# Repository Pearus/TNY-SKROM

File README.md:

# TNY-SKROM

This is a custom SKROM board for the TinyTendo handheld console by <a href="https://github.com/Redherring32">Redherring32</a>. This board replicates <a href="https://www.nesdev.org/wiki/MMC1">standard SKROM NES boards</a>. SKROM uses CHR ROM and PRG RAM, and can have a backup battery if the game saves data on the PRG RAM. You can also make SLROM games with this board and remove the PRG RAM.

To use this board, you must remove an MMC1 mapper from an original NES board, clip the leads flush to the package, sand it, and mount it where U1 is indicated. Since these boards use the 39SF040 for both PRG and CHR ROM, you should use FamiROM or some other utility to duplicate the ROM files to completely fill up the entire space on the Flash chip if necessary.

# TNY-SKROM Board Characteristics

- Thickness: 1.6 mm
- Surface Finish: ENIG
- Chamfered edges (45°)
- Compatible NES board types: SAROM, SBROM, SCROM, SEROM, SFROM, SHROM, SIROM, SJROM, **SKROM**, SLROM
- Compatible NES board types with CHR RAM flex: SGROM, SMROM, SNROM, SUROM

# How to Use This Board

*Note: Do not solder U2 and U3 to the board before programming them.*

SAROM and SKROM games require every component on the board. **DO NOT** solder bridge the pads labelled "NO BATT."

SJROM games are the same as SAROM/SKROM, but without the battery, R1, D1, and D2. You must also bridge the two pads labelled "NO BATT" with solder.

SAROM, SBROM, SCROM, SEROM, SFROM, SHROM, and SLROM games are the same as SJROM, but without U4, R2, R4, C5, and C6. You don't need to bridge the "NO BATT" pads.

SGROM, SMROM, SNROM, and SUROM games require the included flex to fit an SRAM chip in place of the CHR ROM.

The solder jumpers must be bridged according to the NES board type you are trying to replicate.

| Jumper  | SA/SB/SC/SF/SI/SJ/SK/SL | SE/SH  | SG/SM/SU  | SN |
|:-------------------------------------:|:-------------------------------------:|:-------------------------------------:|:-------------------------------------:|:-------------------------------------:|
| CHR ROM  |  |   | Unbridged  | Unbridged  |
| CHR ROM/RAM  |  |   |   |   |
| SNROM  |  |   |   |   |
| SEROM/SHROM  |  |   |   |   |

## Flashing the Game

Prepare the ROM using FamiROM or other similar program, ensuring the entire 4Mbit space is filled for both the PRG and CHR components. You then need to program the 39SF040s before soldering them to the board. I use a <a href="https://www.embeddedcomputers.net/products/FlashcatUSB_XPORT/">FlashCat</a> with a <a href="https://www.embeddedcomputers.net/products/ParallelAdapters/">TSOP-32 adapter (Type B)</a> to achieve this.

# Bill of Materials

Capacitors should be at least 16V rated. Resistor wattage is negligible.

| Reference Designator  | Part Number/Value | Footprint  |
| ------------- | ------------- | ------------- |
| B1  | CR2016 | CR2016  |
| C1  | 22 uF | 1206  |
| C2-C5  | 0.1 uF | 0603  |
| D1, D2  | <a href="https://www.mouser.com/ProductDetail/Vishay-Semiconductors/BAT54W-HG3-18?qs=BJlw7L4Cy79w8lzctLBe5g%3D%3D">BAT54</a> | SMA (SOD-123) |
| R1  | 1 kΩ | 0603  |
| R2  | 27 kΩ | 0603  |
| R3  | 10 kΩ | 0603  |
| U1  | MMC1  | SHRINKDIP24  |
| U2  | <a href="https://www.mouser.com/ProductDetail/Microchip-Technology/SST39SF040-70-4C-WHE?qs=Oo69DRhzroe%2FJKrgAmUE5Q%3D%3D">39SF040</a>  | TSOP32 (14mm) |
| U3 (ROM)  | <a href="https://www.mouser.com/ProductDetail/Microchip-Technology/SST39SF040-70-4C-WHE?qs=Oo69DRhzroe%2FJKrgAmUE5Q%3D%3D">39SF040</a>  | TSOP32 (14mm) |
| U3 (RAM)  | <a href="https://www.mouser.com/ProductDetail/Alliance-Memory/AS6C6264-55STCN?qs=LD2UibpCYJonFY2RVods7g%3D%3D">AS6C6264</a> or <a href="https://www.mouser.com/ProductDetail/870-IS61C64AL-10TLI">IS61C64AL-10TLI</a>  | TSOP28 |
| U4  | <a href="https://www.mouser.com/ProductDetail/Alliance-Memory/AS6C6264-55SCN?qs=LD2UibpCYJq5mmbqgDVBYw%3D%3D">AS6C6264</a>              | SOP28  / SOIC28 |

# Revision History

## v1.0

- Initial version

## License
<br />This work is licensed under a <a rel="license" href="http://creativecommons.org/licenses/by-sa/4.0/">Creative Commons Attribution-ShareAlike 4.0 International License</a>. You are able to copy and redistribute the material in any medium or format, as well as remix, transform, or build upon the material for any purpose (even commercial) - but you **must** give appropriate credit, provide a link to the license, and indicate if any changes were made.

## Credits

*Redherring32* - Creating the TinyTendo project.

*BucketMouse* - Original MMC3 and NROM cartridge designs for TinyTendo which this is an extension of.

*NESDev* - Wiki was heavily referenced as part of writing the schematic and troubleshooting.

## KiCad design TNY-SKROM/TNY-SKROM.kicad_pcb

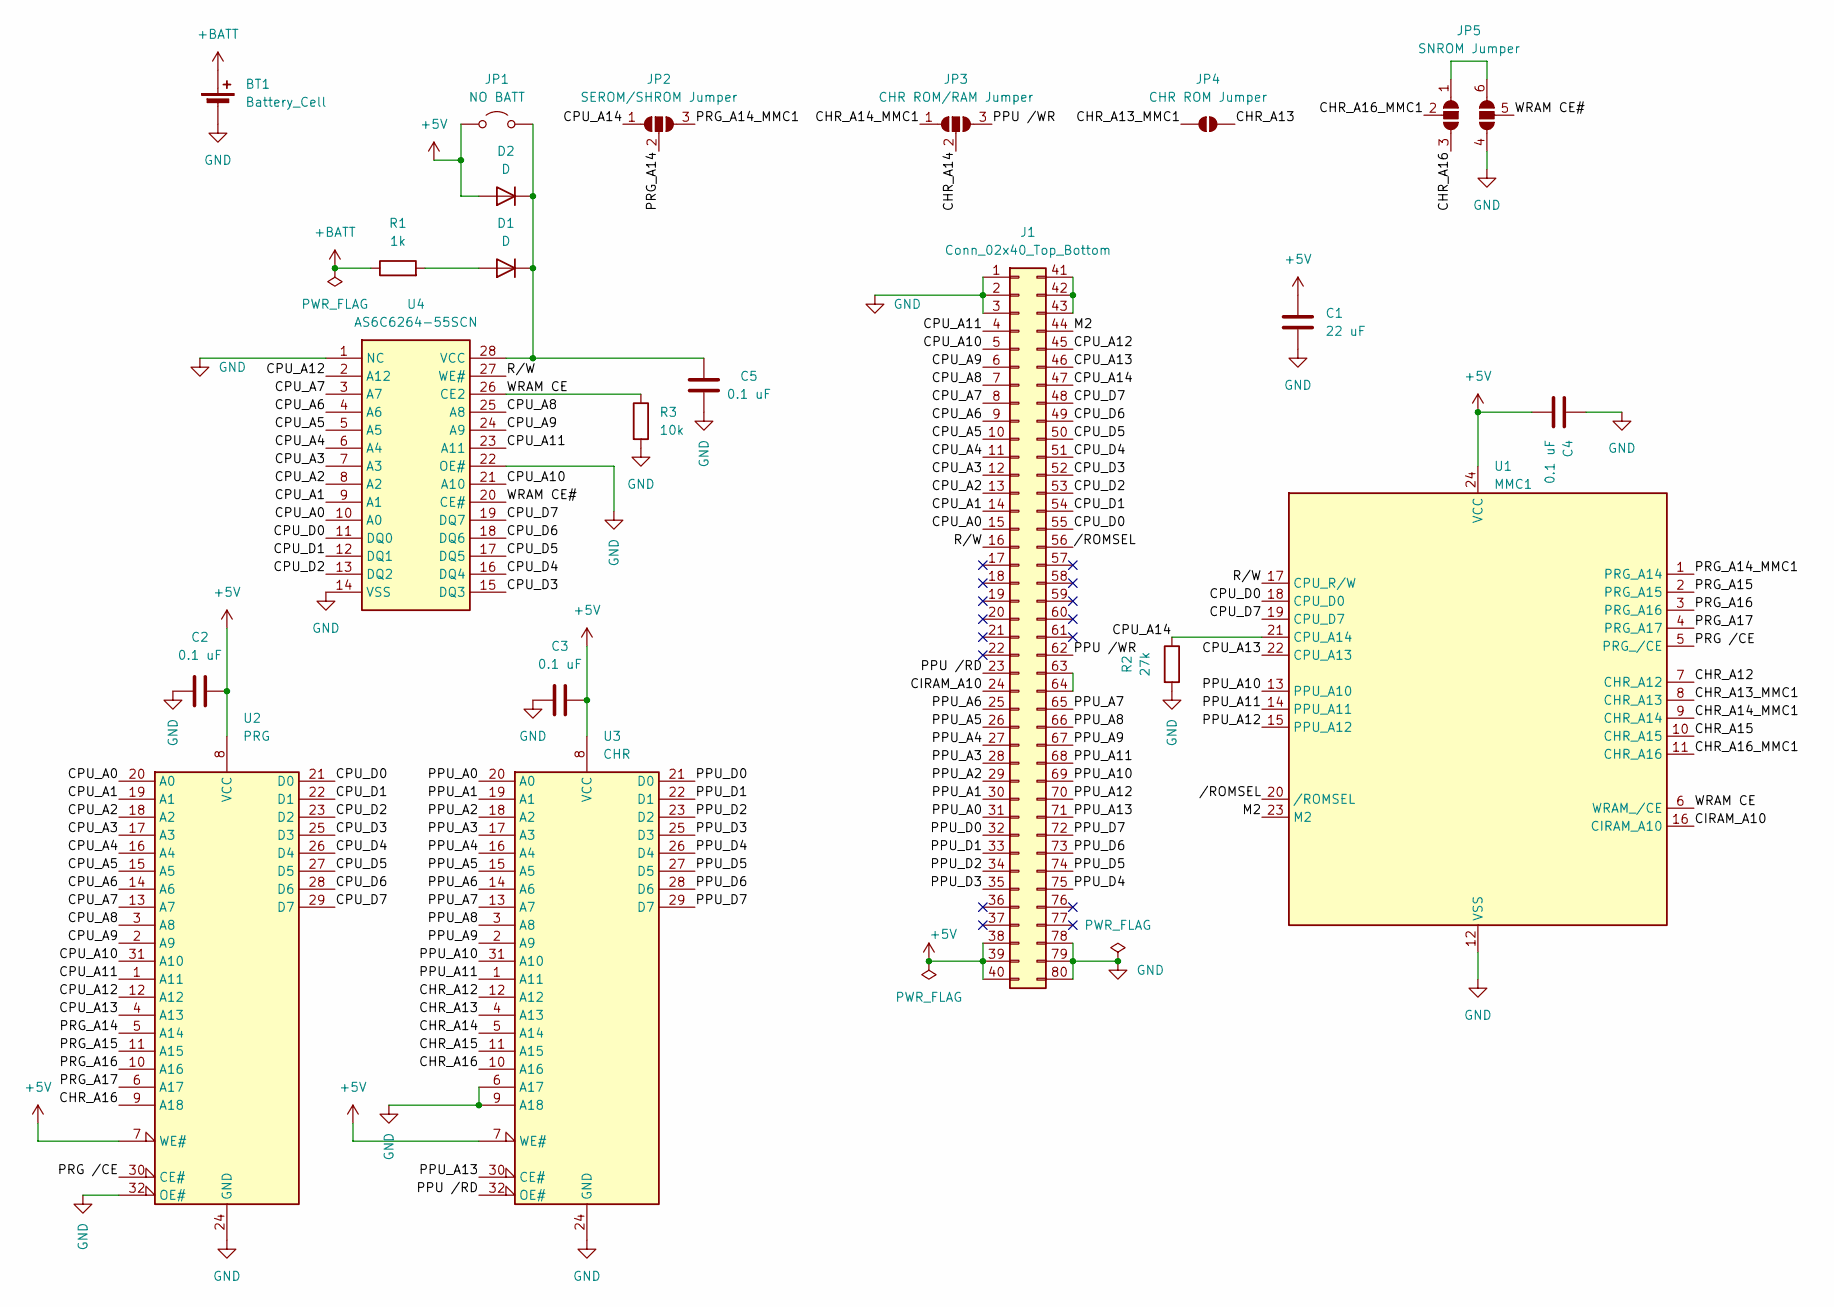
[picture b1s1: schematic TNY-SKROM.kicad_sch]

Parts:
BT1: Battery_Cell; Tabbed CR2016
C1: 22 uF; C_1206_3216Metric
C2, C3, C4, C5: 0.1 uF; C_0603_1608Metric
D1, D2: D; D_SOD-123
J1: Conn_02x40_Top_Bottom; TNY-SKROM Edge Connector
JP1: NO BATT; SolderJumper-2_P1.3mm_Open_Pad1.0x1.5mm
JP2: SEROM/SHROM Jumper; SEROM_SHROM Jumper
JP3: CHR ROM/RAM Jumper; CHR A14 Jumper
JP4: CHR ROM Jumper; CHR A13 Jumper
JP5: SNROM Jumper
R1: 1k; R_0603_1608Metric
R2: 27k; R_0603_1608Metric
R3: 10k; R_0603_1608Metric
U1: MMC1
U2: PRG; TSOP-32
U3: CHR; TSOP-32
U4: AS6C6264-55SCN; Manufacturer_Part_Number AS6C6264-55SCN; Mouser Part Number 913-AS6C6264-55SCN

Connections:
+5V: C1.1, C2.2, C3.1, C4.2, D2.2 (A), J1.38, J1.39, J1.40, JP1.1 (A), U1.24 (VCC), U2.7 (WE#), U2.8 (VCC), U3.7 (WE#), U3.8 (VCC)
+BATT: BT1.1 (+), R1.1
/CHR_A12: U1.7 (CHR_A12), U3.12 (A12)
/CHR_A13: JP4.2 (B), U3.4 (A13)
/CHR_A13_MMC1: JP4.1 (A), U1.8 (CHR_A13)
/CHR_A14: JP3.2 (C), U3.5 (A14)
/CHR_A14_MMC1: JP3.1 (A), U1.9 (CHR_A14)
/CHR_A15: U1.10 (CHR_A15), U3.11 (A15)
/CHR_A16: JP5.3 (B), U2.9 (A18), U3.10 (A16)
/CHR_A16_MMC1: JP5.2 (C), U1.11 (CHR_A16)
/CIRAM_A10: J1.24, U1.16 (CIRAM_A10)
/CPU_A0: J1.15, U2.20 (A0), U4.10 (A0)
/CPU_A1: J1.14, U2.19 (A1), U4.9 (A1)
/CPU_A2: J1.13, U2.18 (A2), U4.8 (A2)
/CPU_A3: J1.12, U2.17 (A3), U4.7 (A3)
/CPU_A4: J1.11, U2.16 (A4), U4.6 (A4)
/CPU_A5: J1.10, U2.15 (A5), U4.5 (A5)
/CPU_A6: J1.9, U2.14 (A6), U4.4 (A6)
/CPU_A7: J1.8, U2.13 (A7), U4.3 (A7)
/CPU_A8: J1.7, U2.3 (A8), U4.25 (A8)
/CPU_A9: J1.6, U2.2 (A9), U4.24 (A9)
/CPU_A10: J1.5, U2.31 (A10), U4.21 (A10)
/CPU_A11: J1.4, U2.1 (A11), U4.23 (A11)
/CPU_A12: J1.45, U2.12 (A12), U4.2 (A12)
/CPU_A13: J1.46, U1.22 (CPU_A13), U2.4 (A13)
/CPU_A14: J1.47, JP2.1 (A), R2.1, U1.21 (CPU_A14)
/CPU_D0: J1.55, U1.18 (CPU_D0), U2.21 (D0), U4.11 (DQ0)
/CPU_D1: J1.54, U2.22 (D1), U4.12 (DQ1)
/CPU_D2: J1.53, U2.23 (D2), U4.13 (DQ2)
/CPU_D3: J1.52, U2.25 (D3), U4.15 (DQ3)
/CPU_D4: J1.51, U2.26 (D4), U4.16 (DQ4)
/CPU_D5: J1.50, U2.27 (D5), U4.17 (DQ5)
/CPU_D6: J1.49, U2.28 (D6), U4.18 (DQ6)
/CPU_D7: J1.48, U1.19 (CPU_D7), U2.29 (D7), U4.19 (DQ7)
/M2: J1.44, U1.23 (M2)
/PPU /RD: J1.23, U3.32 (OE#)
/PPU /WR: J1.62, JP3.3 (B)
/PPU_A0: J1.31, U3.20 (A0)
/PPU_A1: J1.30, U3.19 (A1)
/PPU_A2: J1.29, U3.18 (A2)
/PPU_A3: J1.28, U3.17 (A3)
/PPU_A4: J1.27, U3.16 (A4)
/PPU_A5: J1.26, U3.15 (A5)
/PPU_A6: J1.25, U3.14 (A6)
/PPU_A7: J1.65, U3.13 (A7)
/PPU_A8: J1.66, U3.3 (A8)
/PPU_A9: J1.67, U3.2 (A9)
/PPU_A10: J1.69, U1.13 (PPU_A10), U3.31 (A10)
/PPU_A11: J1.68, U1.14 (PPU_A11), U3.1 (A11)
/PPU_A12: J1.70, U1.15 (PPU_A12)
/PPU_A13: J1.71, U3.30 (CE#)
/PPU_D0: J1.32, U3.21 (D0)
/PPU_D1: J1.33, U3.22 (D1)
/PPU_D2: J1.34, U3.23 (D2)
/PPU_D3: J1.35, U3.25 (D3)
/PPU_D4: J1.75, U3.26 (D4)
/PPU_D5: J1.74, U3.27 (D5)
/PPU_D6: J1.73, U3.28 (D6)
/PPU_D7: J1.72, U3.29 (D7)
/PRG /CE: U1.5 (PRG_/CE), U2.30 (CE#)
/PRG_A14: JP2.2 (C), U2.5 (A14)
/PRG_A14_MMC1: JP2.3 (B), U1.1 (PRG_A14)
/PRG_A15: U1.2 (PRG_A15), U2.11 (A15)
/PRG_A16: U1.3 (PRG_A16), U2.10 (A16)
/PRG_A17: U1.4 (PRG_A17), U2.6 (A17)
/R/W: J1.16, U1.17 (CPU_R/W), U4.27 (WE#)
/WRAM CE: R3.1, U1.6 (WRAM_/CE), U4.26 (CE2)
/WRAM CE#: JP5.5 (C), U4.20 (CE#)
//ROMSEL: J1.56, U1.20 (/ROMSEL)
GND: BT1.2 (-), C1.2, C2.1, C3.2, C4.1, C5.2, J1.1, J1.2, J1.3, J1.78, J1.79, J1.80, JP5.4 (A), R2.2, R3.2, U1.12 (VSS), U2.24 (GND), U2.32 (OE#), U3.6 (A17), U3.9 (A18), U3.24 (GND), U4.1 (NC), U4.14 (VSS), U4.22 (OE#)
unnamed: D1.2 (A), R1.2
unnamed: C5.1, D1.1 (K), D2.1 (K), JP1.2 (B), U4.28 (VCC)
unnamed: J1.41, J1.42, J1.43
unnamed: J1.63, J1.64
unnamed: JP5.1 (A), JP5.6 (B)

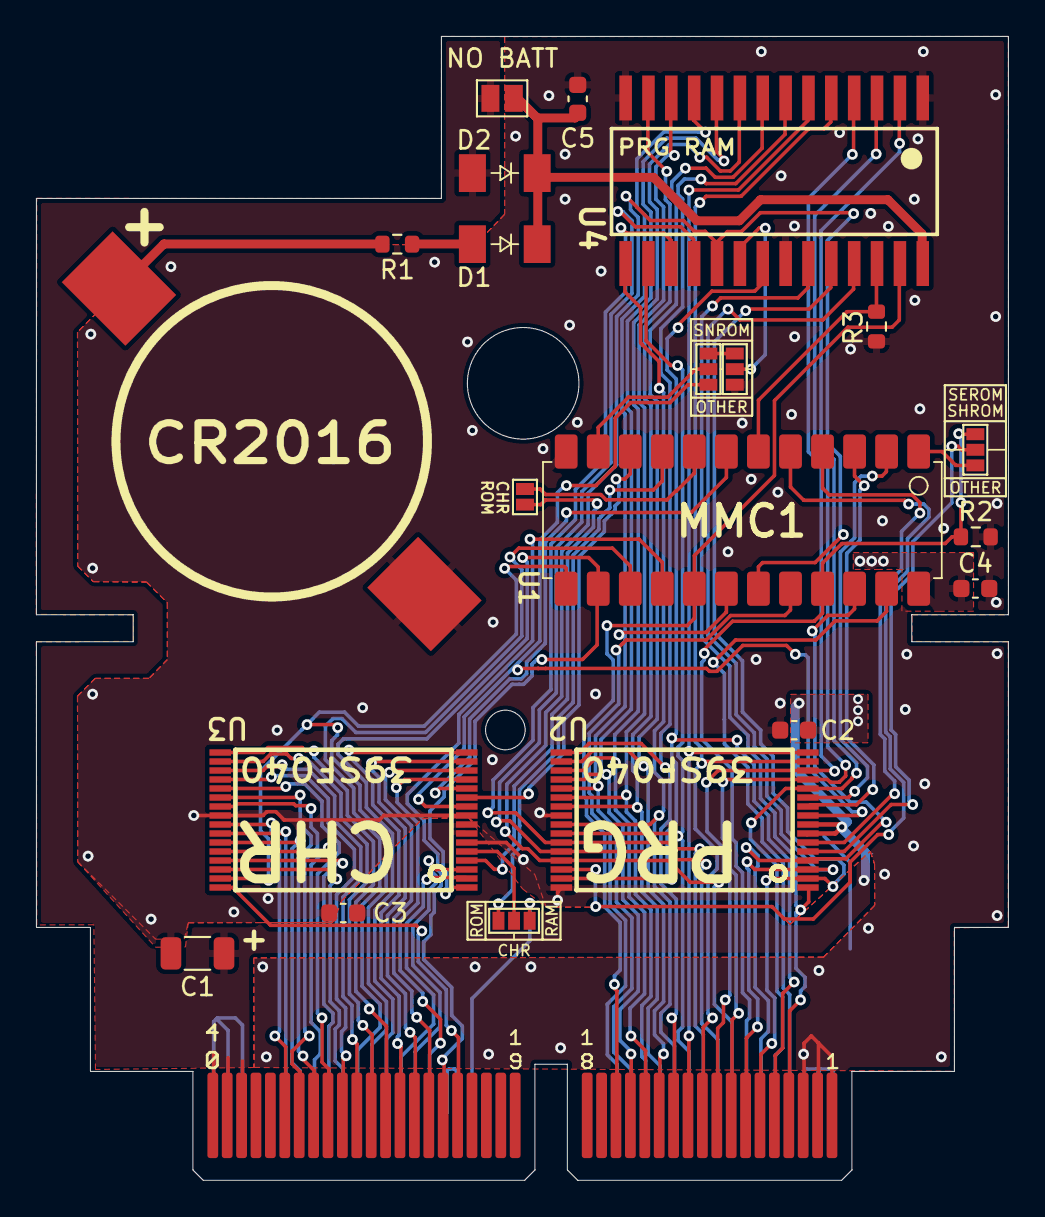
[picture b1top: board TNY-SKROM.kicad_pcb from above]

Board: 2 copper layers, 54.0 x 63.6 mm, 21 parts (0 on the bottom side), 75 nets.

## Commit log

2025-04-23 Update README.md
    Corrected U3 (RAM) part number.
